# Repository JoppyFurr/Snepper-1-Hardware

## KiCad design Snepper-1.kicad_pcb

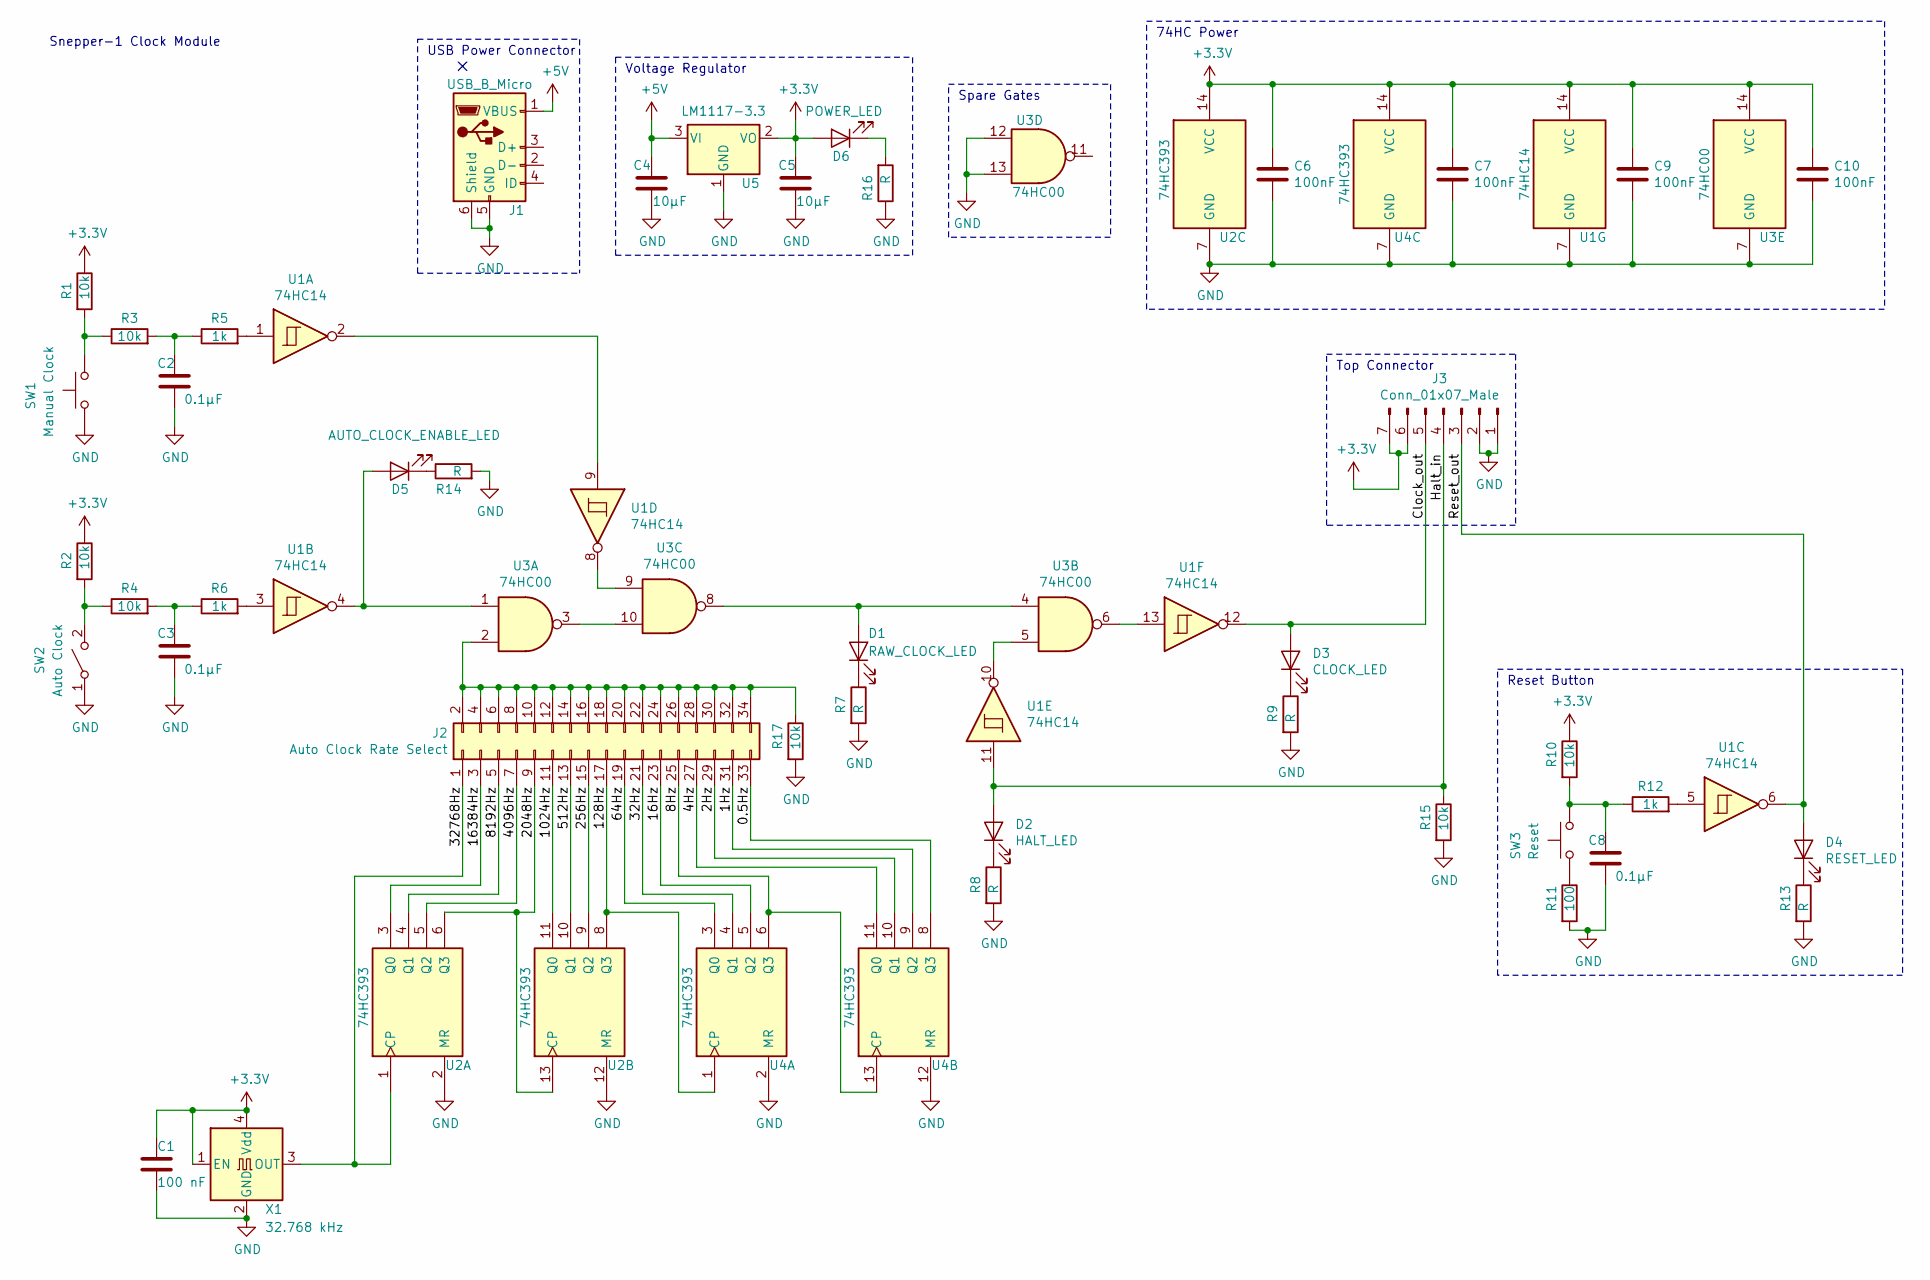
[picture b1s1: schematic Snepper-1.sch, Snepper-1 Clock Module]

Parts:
C1: 100 nF; C_0805_2012Metric_Pad1.15x1.40mm_HandSolder
C2, C3, C8: 0.1µF; C_0805_2012Metric_Pad1.15x1.40mm_HandSolder
C4, C5: 10µF; C_0805_2012Metric_Pad1.15x1.40mm_HandSolder
C6, C7, C9, C10: 100nF; C_0805_2012Metric_Pad1.15x1.40mm_HandSolder
D1: RAW_CLOCK_LED; LED_0805_2012Metric_Pad1.15x1.40mm_HandSolder
D2: HALT_LED; LED_0805_2012Metric_Pad1.15x1.40mm_HandSolder
D3: CLOCK_LED; LED_0805_2012Metric_Pad1.15x1.40mm_HandSolder
D4: RESET_LED; LED_0805_2012Metric_Pad1.15x1.40mm_HandSolder
D5: AUTO_CLOCK_ENABLE_LED; LED_0805_2012Metric_Pad1.15x1.40mm_HandSolder
D6: POWER_LED; LED_0805_2012Metric_Pad1.15x1.40mm_HandSolder
J1: USB_B_Micro; USB_Micro-B_Molex-105017-0001
J2: Auto Clock Rate Select; PinHeader_2x17_P2.54mm_Vertical
J3: Conn_01x07_Male; PinHeader_1x07_P2.54mm_Horizontal
R1, R2, R3, R4, R10, R15, R17: 10k; R_0805_2012Metric_Pad1.15x1.40mm_HandSolder
R5, R6, R12: 1k; R_0805_2012Metric_Pad1.15x1.40mm_HandSolder
R7, R8, R9, R13, R14, R16: R; R_0805_2012Metric_Pad1.15x1.40mm_HandSolder
R11: 100; R_0805_2012Metric_Pad1.15x1.40mm_HandSolder
SW1: Manual Clock; Switch_Tactile_THT_6x6mm
SW2: Auto Clock; Switch_12.7mm_XKB
SW3: Reset; Switch_Tactile_THT_6x6mm
U1: 74HC14; SOIC-14_3.9x8.7mm_P1.27mm
U2, U4: 74HC393; SOIC-14_3.9x8.7mm_P1.27mm
U3: 74HC00; SOIC-14_3.9x8.7mm_P1.27mm
U5: LM1117-3.3; SOT-223
X1: 32.768 kHz; Oscillator_SMD_Abracon_ASE-4Pin_3.2x2.5mm

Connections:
+3V3: C1.1, C5.1, C6.1, C7.1, C9.1, C10.1, D6.2 (A), J3.6, J3.7, R1.1, R2.1, R10.1, U1.14 (VCC), U2.14 (VCC), U3.14 (VCC), U4.14 (VCC), U5.2 (VO), X1.1 (EN), X1.4 (Vdd)
+5V: C4.2, J1.1 (VBUS), U5.3 (VI)
/0.5Hz: J2.33, U4.8 (Q3)
/1Hz: J2.31, U4.9 (Q2)
/2Hz: J2.29, U4.10 (Q1)
/4Hz: J2.27, U4.11 (Q0)
/8Hz: J2.25, U4.6 (Q3), U4.13 (CP)
/16Hz: J2.23, U4.5 (Q2)
/32Hz: J2.21, U4.4 (Q1)
/64Hz: J2.19, U4.3 (Q0)
/128Hz: J2.17, U2.8 (Q3), U4.1 (CP)
/256Hz: J2.15, U2.9 (Q2)
/512Hz: J2.13, U2.10 (Q1)
/1024Hz: J2.11, U2.11 (Q0)
/2048Hz: J2.9, U2.6 (Q3), U2.13 (CP)
/4096Hz: J2.7, U2.5 (Q2)
/8192Hz: J2.5, U2.4 (Q1)
/16384Hz: J2.3, U2.3 (Q0)
/32768Hz: J2.1, U2.1 (CP), X1.3 (OUT)
/Clock_out: D3.2 (A), J3.5, U1.12
/Halt_in: D2.2 (A), J3.4, R15.1, U1.11
/Reset_out: D4.2 (A), J3.3, U1.6
GND: C1.2, C2.2, C3.2, C4.1, C5.2, C6.2, C7.2, C8.2, C9.2, C10.2, J1.5 (GND), J1.6 (Shield), J3.1, J3.2, R7.2, R8.2, R9.2, R11.2, R13.2, R14.2, R15.2, R16.1, R17.2, SW1.1, SW2.1 (A), U1.7 (GND), U2.2 (MR), U2.7 (GND), U2.12 (MR), U3.7 (GND), U3.12, U3.13, U4.2 (MR), U4.7 (GND), U4.12 (MR), U5.1 (GND), X1.2 (GND); also elsewhere on the board
unnamed: C2.1, R3.2, R5.1
unnamed: C3.1, R4.2, R6.1
unnamed: C8.1, R10.2, R12.1, SW3.2
unnamed: D1.1 (K), R7.1
unnamed: D1.2 (A), U3.4, U3.8
unnamed: D2.1 (K), R8.1
unnamed: D3.1 (K), R9.1
unnamed: D4.1 (K), R13.1
unnamed: D5.1 (K), R14.1
unnamed: D5.2 (A), U1.4, U3.1
unnamed: D6.1 (K), R16.2
unnamed: J2.2, J2.4, J2.6, J2.8, J2.10, J2.12, J2.14, J2.16, J2.18, J2.20, J2.22, J2.24, J2.26, J2.28, J2.30, J2.32, J2.34, R17.1, U3.2
unnamed: R1.2, R3.1, SW1.2
unnamed: R2.2, R4.1, SW2.2 (B)
unnamed: R5.2, U1.1
unnamed: R6.2, U1.3
unnamed: R11.1, SW3.1
unnamed: R12.2, U1.5
unnamed: U1.2, U1.9
unnamed: U1.8, U3.9
unnamed: U1.10, U3.5
unnamed: U1.13, U3.6
unnamed: U3.3, U3.10

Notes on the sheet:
Voltage Regulator
USB Power Connector
Spare Gates
Reset Button
74HC Power
Top Connector
Snepper-1 Clock Module

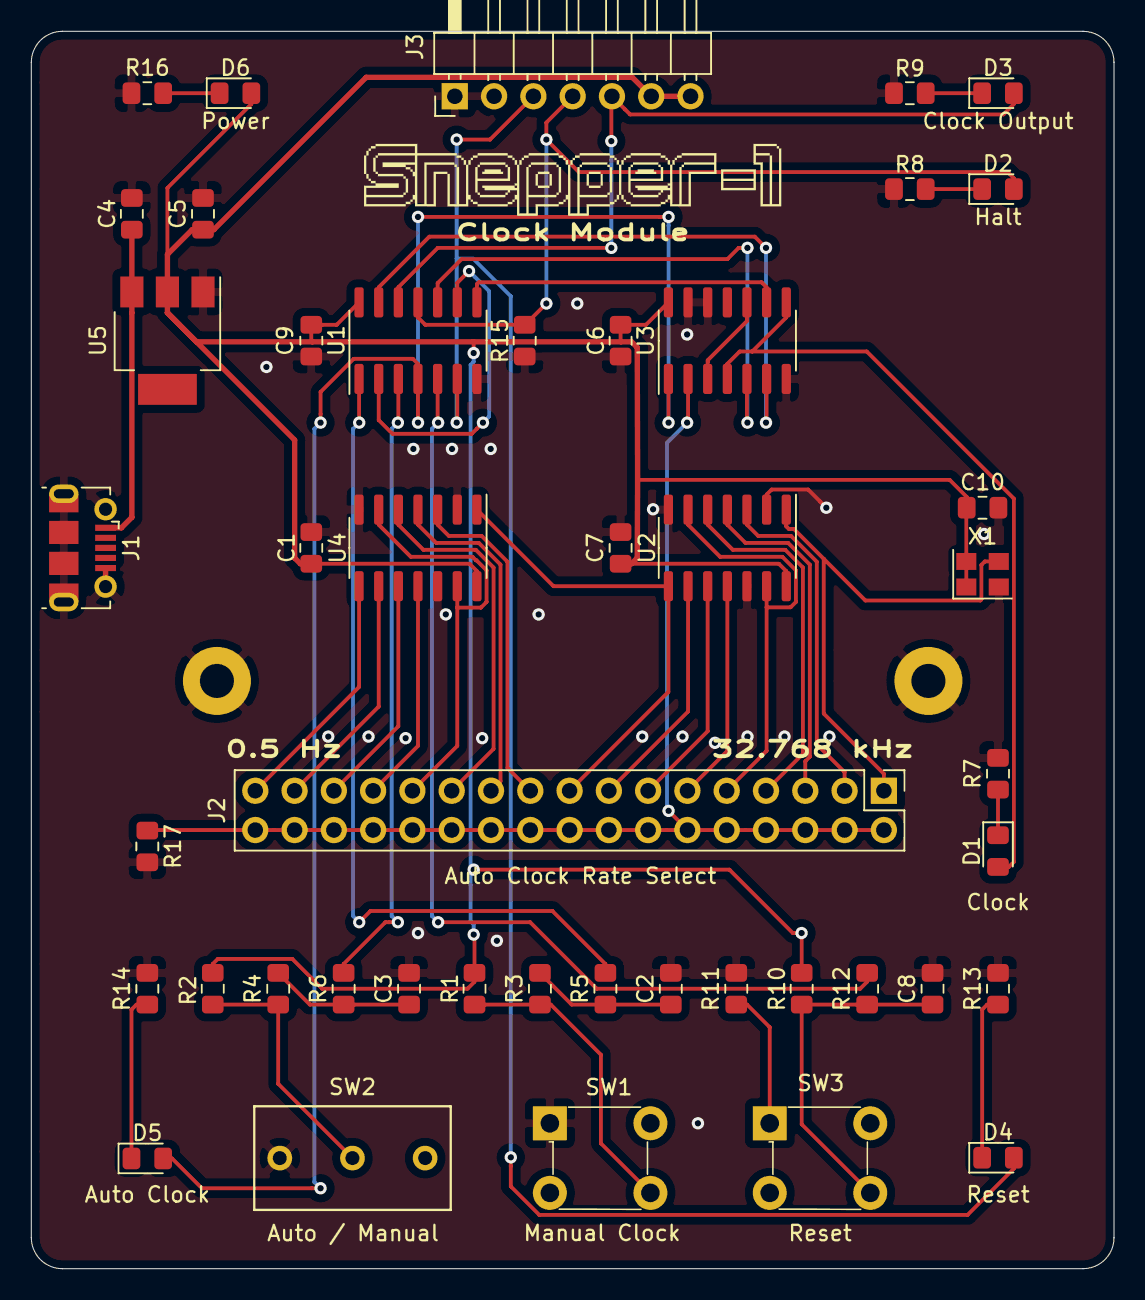
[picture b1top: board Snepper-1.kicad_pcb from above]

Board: 2 copper layers, 70.0 x 80.0 mm, 48 parts (0 on the bottom side), 46 nets.

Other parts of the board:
 : MountingHole_2.2mm_M2_Pad
 #2: MountingHole_2.2mm_M2_Pad
svg2mod: G***; snepper

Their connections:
GND: .1, #2.1; also elsewhere on the board

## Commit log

2020-02-17 First Gerbers generated
2020-03-08 Directory restructure
2020-03-08 Module Layout
